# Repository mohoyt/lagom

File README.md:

# lagom
Lagom is an easy to build 65% keyboard using only through hole components. It uses a separate microcontroller (like the Pro Micro, Elite C or something RP2040 based) to enable flexibility in firmware and connectivity and to further simplify the soldering experience (no more tricksy USB ports). Demultiplexers and a custom matrix are used to enable the size and features of the board with only the pinouts of a pro micro. 

**Lagom kits are available for sale at [sthlmkb.com](https://sthlmkb.com/shop/lagom-keyboard-kit/)**

[License](LICENSE)

Lagom is licensed under the [Creative Commons Attribution-NonCommercial 4.0 International license](https://creativecommons.org/licenses/by-nc/4.0/). This design as it stands in this repository may be freely reproduced, modified, and manufactured for PERSONAL USE ONLY and may not be reproduced in physical form for public sale. 

## Features
* Only through hole components for easy soldering
* Separate microcontroller using Pro micro, Elite C, Nice! Nano or equivalent footprint. So micro USB, USB-C or Bluetooth are all options!
* 2 rotary encoders
* OLED screen
* Optional underglow RGB lighting with a WS2812b light strip
* Multiple layout options including ISO, ANSI, split space (2.25u + 1.25u + 2.75u), 7u space, split left shift (1.25u + 1u) and stepped capslock ([layout]("http://www.keyboard-layout-editor.com/##@_name=Lagom&notes=16%20cols%20%2F=%204%20pins%20with%202x%203%20to%208%20demux%20(2%5E4%20%2F=%2016)%0A5%20rows%0A11%20pins%20total%20for%20keyswitches%0A16%20+%202%20pins%20(for%20OLED)%20on%20a%20pro%20micro%0A1%20pin%20for%20LED%20underglow%0A4%20pins%20for%202%20encoders%0A%0A72%20keys%20+%202%20enc%20%3B&@_x:13.75%3B&=1,15&_x:0.25%3B&=2,15&_x:0.25%3B&=0,0%0A%0A%0A%0A%0A%0A%0A%0A%0Ae&=0,1%0A%0A%0A%0A%0A%0A%0A%0A%0Ae%3B&@_y:0.25%3B&=0,0&=0,1&=0,2&=0,3&=0,4&=0,5&=0,6&=0,7&=0,8&=0,9&=0,10&=0,11&=0,12&_w:2%3B&=0,14%0A%0A%0A0,0&=0,15&_x:0.25%3B&=1,0%0A%0A%0A%0A%0A%0A%0A%0A%0Ae&=1,1%0A%0A%0A%0A%0A%0A%0A%0A%0Ae%3B&@_w:1.5%3B&=1,0&=1,1&=1,2&=1,3&=1,4&=1,5&=1,6&=1,7&=1,8&=1,9&=1,10&=1,11&=1,12&_w:1.5%3B&=1,13%0A%0A%0A1,0&=1,14%3B&@_w:1.75%3B&=2,0&=2,1&=2,2&=2,3&=2,4&=2,5&=2,6&=2,7&=2,8&=2,9&=2,10&=2,11&_w:2.25%3B&=2,13%0A%0A%0A1,0&=2,14%3B&@_w:2.25%3B&=3,0%0A%0A%0A2,0&=3,2&=3,3&=3,4&=3,5&=3,6&=3,7&=3,8&=3,9&=3,10&=3,11&_w:1.75%3B&=3,12&=3,13&=3,14%3B&@_w:1.25%3B&=4,0%0A%0A%0A3,0&_w:1.25%3B&=4,1%0A%0A%0A3,0&_w:1.25%3B&=4,2%0A%0A%0A3,0&_w:6.25%3B&=4,6%0A%0A%0A3,0&_w:1.25%3B&=4,10%0A%0A%0A3,0&_w:1.25%3B&=4,11%0A%0A%0A3,0&_x:0.5%3B&=4,12&=4,13&=4,14%3B&@_y:0.5&w:1.25%3B&=4,0%0A%0A%0A3,1&_w:1.25%3B&=4,1%0A%0A%0A3,1&_w:1.25%3B&=4,2%0A%0A%0A3,1&_w:2.25%3B&=4,4%0A%0A%0A3,1&_w:1.25%3B&=4,6%0A%0A%0A3,1&_w:2.75%3B&=4,8%0A%0A%0A3,1&_w:1.25%3B&=4,10%0A%0A%0A3,1&_w:1.25%3B&=4,11%0A%0A%0A3,1%3B&@_y:-0.25&x:15&w:1.25&h:2&w2:1.5&h2:1&x2:-0.25%3B&=2,13%0A%0A%0A1,1%3B&@_y:-0.75&w:1.5%3B&=4,0%0A%0A%0A3,2&=4,1%0A%0A%0A3,2&_w:1.5%3B&=4,2%0A%0A%0A3,2&_w:7%3B&=4,6%0A%0A%0A3,2&_w:1.5%3B&=4,11%0A%0A%0A3,2%3B&@_y:-0.25&x:14%3B&=2,12%0A%0A%0A1,1%3B&@_w:1.25%3B&=3,0%0A%0A%0A2,1&=3,1%0A%0A%0A2,1&_x:9.75%3B&=0,13%0A%0A%0A0,1&=0,14%0A%0A%0A0,1"))
* Open and visible components (in the style of Plaid, Romac etc)
* Simple, beautiful and flexible sandwich case out of FR4 (pcb material)

## Components required 
* PCB
* FR4 Switch plate
* FR4 Base 
* Controller (I used a Pro Micro in the guide but anything that shares the footprint and pinout will be fine e.g. Elite C, Nice! Nano, or something RP2040 powered!)
* Diodes 1N4148 (74)
* 0.1μF Capacitor (2)
* 16 pin IC socket (2)
* IC (74HC138N) demultiplexer (2)
* Switches (5 pin MX footprint) (up to 72 depending on layout)
* Rotary encoders (2)
* Rotary encoder knobs (2)
* 0.91" OLED screen
* 10mm M2 Standoffs (9 required if mounting the base to the plate)
* 6mm x M2 screws for attaching the standoffs to the plate/base (2 per standoff so 18 total)
* Acrylic cover for the components at the top (optional, not included)
* Stabilisers (PCB mount) (5 x 2u or 3 x 2u + 6.25u or 3 x 2u + 7u depending on layout)
* Rubber feet for the base

[Build guide available here](build_guide.md)

## Dimensions
* PCB: 305.6mm x 121.78mm
* Plate: 319.925mm x 128.925mm (102.662mm height at the lower section)
* Base: 319.925mm x 128.925mm 

## Known issues 
None yet! 

## Where to buy
Lagom kits are available for sale exclusively at [sthlmkb.com](https://sthlmkb.com/shop/lagom-keyboard-kit/)

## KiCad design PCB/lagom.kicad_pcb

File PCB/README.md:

# lagom PCBs
Lagom is an easy to build 65% keyboard using only through hole components. It uses a separate microcontroller (like the Pro Micro, Elite C or something RP2040 based) to enable flexibility in firmware and connectivity and to further simplify the soldering experience (no more tricksy USB ports). Demultiplexers and a custom matrix are used to enable the size and features of the board with only the pinouts of a pro micro. 

**Lagom kits are available for sale at [sthlmkb.com](https://sthlmkb.com/shop/lagom-keyboard-kit/)**

[License](LICENSE)

Lagom is licensed under the [Creative Commons Attribution-NonCommercial 4.0 International license](https://creativecommons.org/licenses/by-nc/4.0/). This design as it stands in this repository may be freely reproduced, modified, and manufactured for PERSONAL USE ONLY and may not be reproduced in physical form for public sale. 

## Designs that are here:
* Lagom (i.e this directory) - this is the main PCB
* Lagom Plate (`lagom_plate`) - this is the plate that holds the switches and goes above the PCB
* Lagom Base (`lagom_base`) - this is the base of the board and goes below the PCB
* Lagom Window (`lagom_window`) - this is an optional design for an acrylic window that covers the diodes and the controller

## Some useful images/documentation:

This the key layout and all option layouts exported from keyboard-layout-editor

This the layout of the matrix used

This the pinout of the pro micro or pro micro compatible controller

This is the pinout of the demuxes used in Lagom to enable all the columns to work on a pro micro pinout

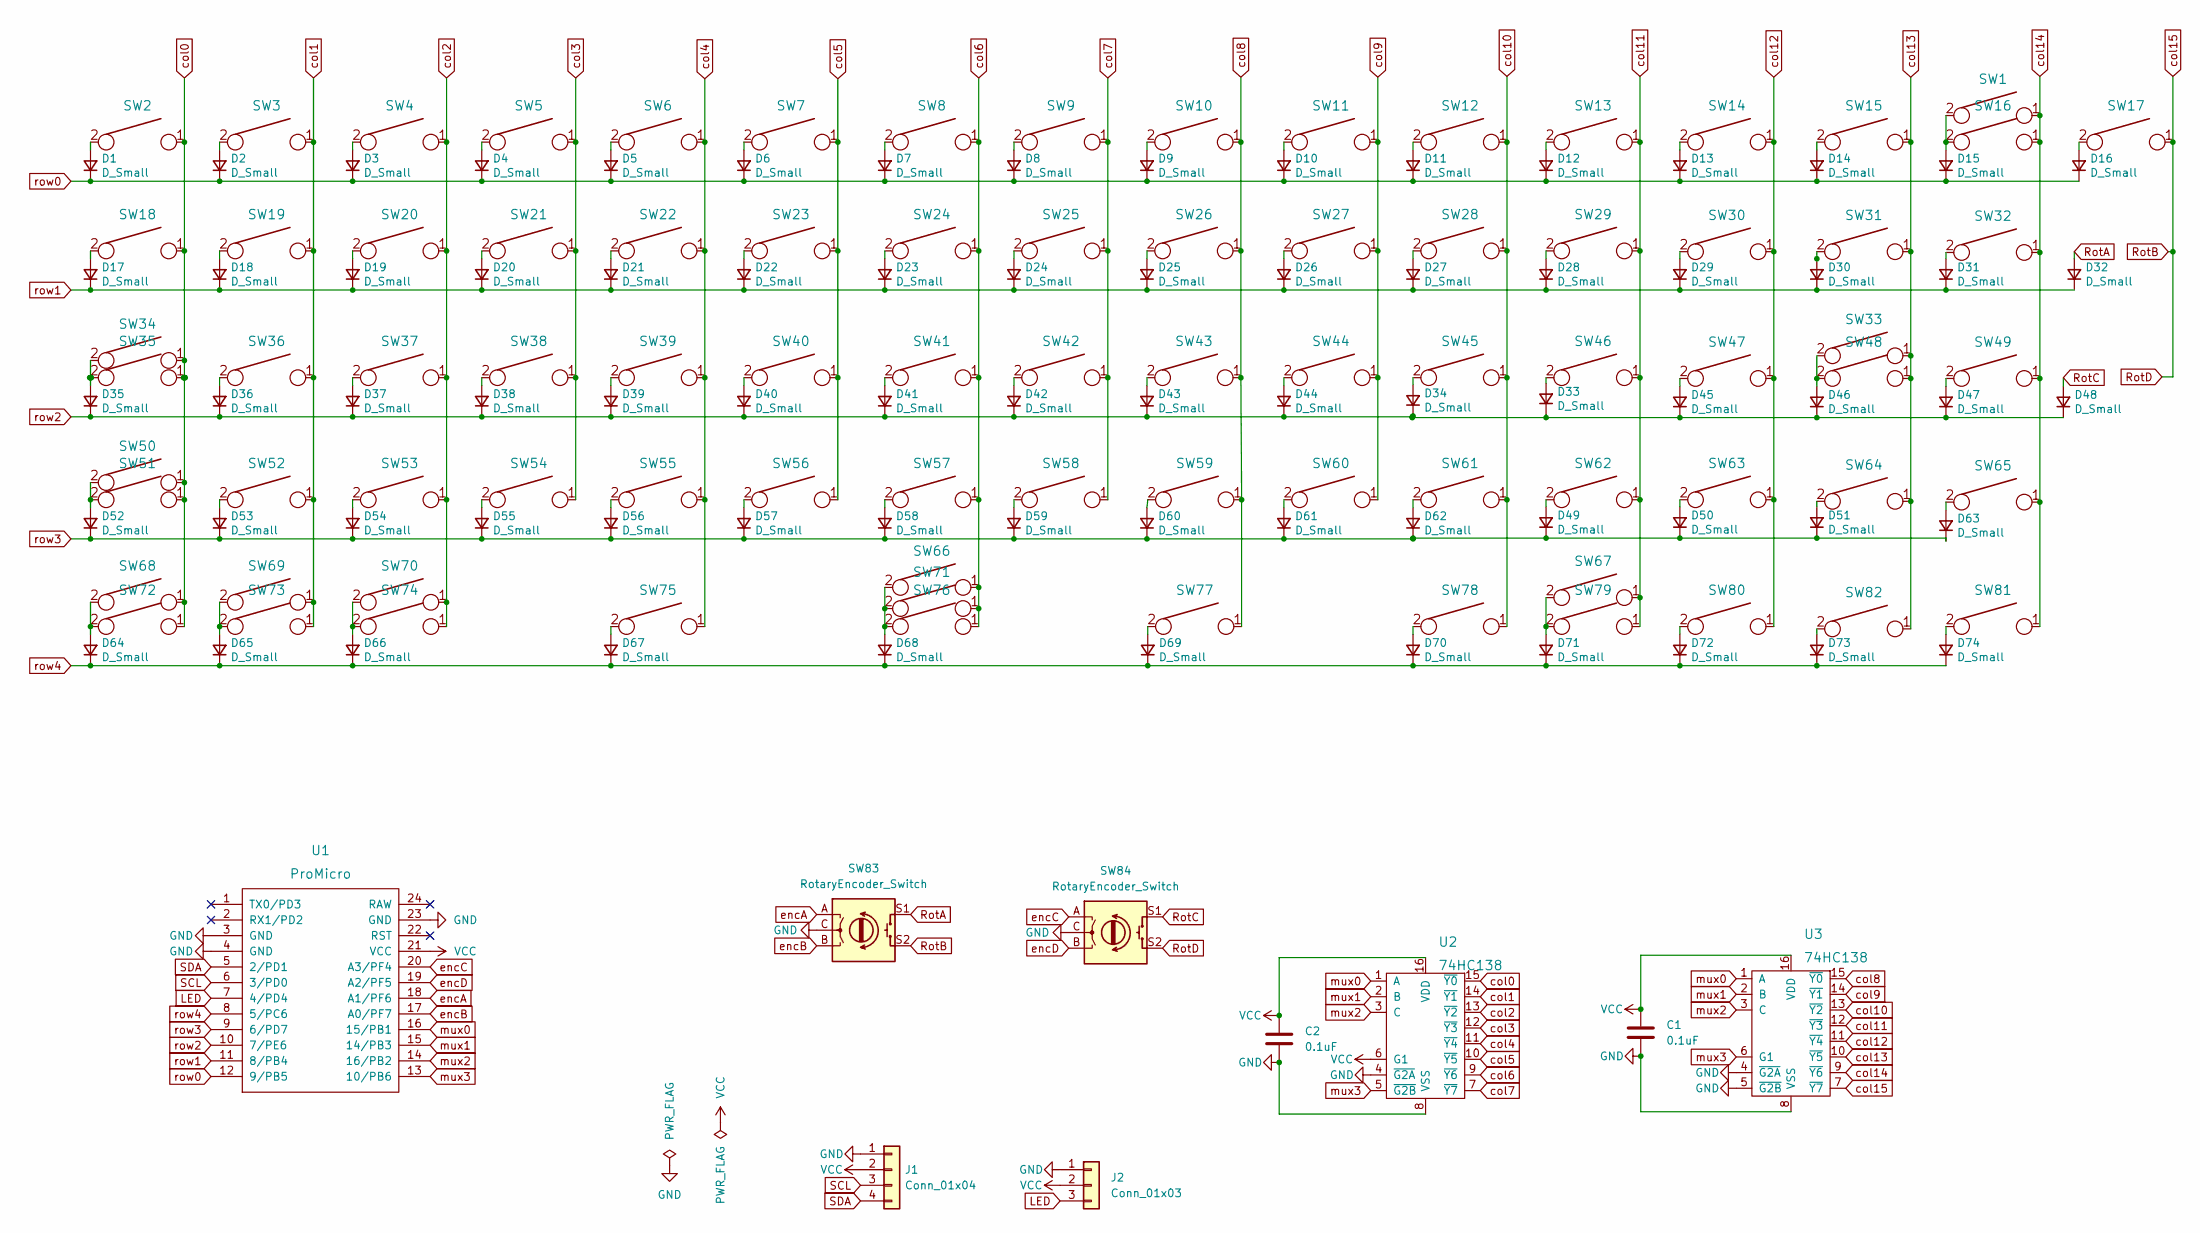
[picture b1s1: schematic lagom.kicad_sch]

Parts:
C1, C2: 0.1uF; C_Disc_D4.7mm_W2.5mm_P5.00mm
D1: D_Small; D_DO-35_SOD27_P7.62mm_Horizontal
D2, D3, D4, D5, D6, D7, D8, D9, D10, D11, D12, D13, D14, D15, D16, D17, D18, D19, D20, D21, D22, D23, D24, D25, D26, D27, D28, D29, D30, D31, D32, D33, D34, D35, D36, D37, D38, D39, D40, D41, D42, D43, D44, D45, D46, D47, D48, D49, D50, D51, D52, D53, D54, D55, D56, D57, D58, D59, D60, D61, D62, D63, D64, D65, D66, D67, D68, D69, D70, D71, D72, D73, D74: D_Small; D_DO-34_SOD68_P7.62mm_Horizontal
J1: Conn_01x04; PinSocket_1x04_P2.54mm_Vertical
J2: Conn_01x03; PinSocket_1x03_P2.54mm_Vertical
SW1: KEYSW; SW_Cherry_MX_2.00u_PCB
SW2, SW3, SW4, SW5, SW6, SW7, SW8, SW9, SW10, SW11, SW12, SW13, SW14, SW15, SW16, SW17, SW19, SW20, SW21, SW22, SW23, SW24, SW25, SW26, SW27, SW28, SW29, SW30, SW32, SW35, SW36, SW37, SW38, SW39, SW40, SW41, SW42, SW43, SW44, SW45, SW46, SW47, SW49, SW52, SW53, SW54, SW55, SW56, SW57, SW58, SW59, SW60, SW61, SW62, SW64, SW65, SW73, SW80, SW81, SW82: KEYSW; SW_Cherry_MX_1.00u_PCB
SW18: KEYSW; SW_Cherry_MX_1.50u_Plate
SW31, SW67, SW70, SW72: KEYSW; SW_Cherry_MX_1.50u_PCB
SW33: KEYSW; SW_Cherry_MX_ISOEnter_PCB
SW34, SW63: KEYSW; SW_Cherry_MX_1.75u_PCB
SW48, SW50, SW75: KEYSW; SW_Cherry_MX_2.25u_PCB
SW51, SW68, SW69, SW71, SW74, SW78, SW79: KEYSW; SW_Cherry_MX_1.25u_PCB
SW66: KEYSW; SW_Cherry_MX_7u_PCB
SW76: KEYSW; SW_Cherry_MX_6.25u_PCB
SW77: KEYSW; SW_Cherry_MX_2.75u_PCB
SW83, SW84: RotaryEncoder_Switch; RotaryEncoder_EC11
U1: ProMicro; ArduinoProMicro-ZigZag
U2, U3: 74HC138; DIP-16_W7.62mm_Socket

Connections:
GND: C1.2, C2.2, J1.1, J2.1, SW83.C, SW84.C, U1.3 (GND), U1.4 (GND), U1.23 (GND), U2.4 (~G2A), U2.8 (VSS), U3.4 (~G2A), U3.5 (~G2B), U3.8 (VSS)
LED: J2.3, U1.7 (4/PD4)
unnamed: D1.2 (A), SW2.2
unnamed: D2.2 (A), SW3.2
unnamed: D3.2 (A), SW4.2
unnamed: D4.2 (A), SW5.2
unnamed: D5.2 (A), SW6.2
unnamed: D6.2 (A), SW7.2
unnamed: D7.2 (A), SW8.2
unnamed: D8.2 (A), SW9.2
unnamed: D9.2 (A), SW10.2
unnamed: D10.2 (A), SW11.2
unnamed: D11.2 (A), SW12.2
unnamed: D12.2 (A), SW13.2
unnamed: D13.2 (A), SW14.2
unnamed: D14.2 (A), SW15.2
unnamed: D15.2 (A), SW1.2, SW16.2
unnamed: D16.2 (A), SW17.2
unnamed: D17.2 (A), SW18.2
unnamed: D18.2 (A), SW19.2
unnamed: D19.2 (A), SW20.2
unnamed: D20.2 (A), SW21.2
unnamed: D21.2 (A), SW22.2
unnamed: D22.2 (A), SW23.2
unnamed: D23.2 (A), SW24.2
unnamed: D24.2 (A), SW25.2
unnamed: D25.2 (A), SW26.2
unnamed: D26.2 (A), SW27.2
unnamed: D27.2 (A), SW28.2
unnamed: D28.2 (A), SW29.2
unnamed: D29.2 (A), SW30.2
unnamed: D30.2 (A), SW31.2
unnamed: D31.2 (A), SW32.2
unnamed: D33.2 (A), SW46.2
unnamed: D34.2 (A), SW45.2
unnamed: D35.2 (A), SW34.2, SW35.2
unnamed: D36.2 (A), SW36.2
unnamed: D37.2 (A), SW37.2
unnamed: D38.2 (A), SW38.2
unnamed: D39.2 (A), SW39.2
unnamed: D40.2 (A), SW40.2
unnamed: D41.2 (A), SW41.2
unnamed: D42.2 (A), SW42.2
unnamed: D43.2 (A), SW43.2
unnamed: D44.2 (A), SW44.2
unnamed: D45.2 (A), SW47.2
unnamed: D46.2 (A), SW33.2, SW48.2
unnamed: D47.2 (A), SW49.2
unnamed: D49.2 (A), SW62.2
unnamed: D50.2 (A), SW63.2
unnamed: D51.2 (A), SW64.2
unnamed: D52.2 (A), SW50.2, SW51.2
unnamed: D53.2 (A), SW52.2
unnamed: D54.2 (A), SW53.2
unnamed: D55.2 (A), SW54.2
unnamed: D56.2 (A), SW55.2
unnamed: D57.2 (A), SW56.2
unnamed: D58.2 (A), SW57.2
unnamed: D59.2 (A), SW58.2
unnamed: D60.2 (A), SW59.2
unnamed: D61.2 (A), SW60.2
unnamed: D62.2 (A), SW61.2
unnamed: D63.2 (A), SW65.2
unnamed: D64.2 (A), SW68.2, SW72.2
unnamed: D65.2 (A), SW69.2, SW73.2
unnamed: D66.2 (A), SW70.2, SW74.2
unnamed: D67.2 (A), SW75.2
unnamed: D68.2 (A), SW66.2, SW71.2, SW76.2
unnamed: D69.2 (A), SW77.2
unnamed: D70.2 (A), SW78.2
unnamed: D71.2 (A), SW67.2, SW79.2
unnamed: D72.2 (A), SW80.2
unnamed: D73.2 (A), SW82.2
unnamed: D74.2 (A), SW81.2
RotA: D32.2 (A), SW83.S1
RotB: SW17.1, SW83.S2, SW84.S2, U3.7 (~Y7)
RotC: D48.2 (A), SW84.S1
SCL: J1.3, U1.6 (3/PD0)
SDA: J1.4, U1.5 (2/PD1)
VCC: C1.1, C2.1, J1.2, J2.2, U1.21 (VCC), U2.6 (G1), U2.16 (VDD), U3.16 (VDD)
col0: SW2.1, SW18.1, SW34.1, SW35.1, SW50.1, SW51.1, SW68.1, SW72.1, U2.15 (~Y0)
col1: SW3.1, SW19.1, SW36.1, SW52.1, SW69.1, SW73.1, U2.14 (~Y1)
col2: SW4.1, SW20.1, SW37.1, SW53.1, SW70.1, SW74.1, U2.13 (~Y2)
col3: SW5.1, SW21.1, SW38.1, SW54.1, U2.12 (~Y3)
col4: SW6.1, SW22.1, SW39.1, SW55.1, SW75.1, U2.11 (~Y4)
col5: SW7.1, SW23.1, SW40.1, SW56.1, U2.10 (~Y5)
col6: SW8.1, SW24.1, SW41.1, SW57.1, SW66.1, SW71.1, SW76.1, U2.9 (~Y6)
col7: SW9.1, SW25.1, SW42.1, SW58.1, U2.7 (~Y7)
col8: SW10.1, SW26.1, SW43.1, SW59.1, SW77.1, U3.15 (~Y0)
col9: SW11.1, SW27.1, SW44.1, SW60.1, U3.14 (~Y1)
col10: SW12.1, SW28.1, SW45.1, SW61.1, SW78.1, U3.13 (~Y2)
col11: SW13.1, SW29.1, SW46.1, SW62.1, SW67.1, SW79.1, U3.12 (~Y3)
col12: SW14.1, SW30.1, SW47.1, SW63.1, SW80.1, U3.11 (~Y4)
col13: SW15.1, SW31.1, SW33.1, SW48.1, SW64.1, SW82.1, U3.10 (~Y5)
col14: SW1.1, SW16.1, SW32.1, SW49.1, SW65.1, SW81.1, U3.9 (~Y6)
encA: SW83.A, U1.18 (A1/PF6)
encB: SW83.B, U1.17 (A0/PF7)
encC: SW84.A, U1.20 (A3/PF4)
encD: SW84.B, U1.19 (A2/PF5)
mux0: U1.16 (15/PB1), U2.1 (A), U3.1 (A)
mux1: U1.15 (14/PB3), U2.2 (B), U3.2 (B)
mux2: U1.14 (16/PB2), U2.3 (C), U3.3 (C)
mux3: U1.13 (10/PB6), U2.5 (~G2B), U3.6 (G1)
row0: D1.1 (K), D2.1 (K), D3.1 (K), D4.1 (K), D5.1 (K), D6.1 (K), D7.1 (K), D8.1 (K), D9.1 (K), D10.1 (K), D11.1 (K), D12.1 (K), D13.1 (K), D14.1 (K), D15.1 (K), D16.1 (K), U1.12 (9/PB5)
row1: D17.1 (K), D18.1 (K), D19.1 (K), D20.1 (K), D21.1 (K), D22.1 (K), D23.1 (K), D24.1 (K), D25.1 (K), D26.1 (K), D27.1 (K), D28.1 (K), D29.1 (K), D30.1 (K), D31.1 (K), D32.1 (K), U1.11 (8/PB4)
row2: D33.1 (K), D34.1 (K), D35.1 (K), D36.1 (K), D37.1 (K), D38.1 (K), D39.1 (K), D40.1 (K), D41.1 (K), D42.1 (K), D43.1 (K), D44.1 (K), D45.1 (K), D46.1 (K), D47.1 (K), D48.1 (K), U1.10 (7/PE6)
row3: D49.1 (K), D50.1 (K), D51.1 (K), D52.1 (K), D53.1 (K), D54.1 (K), D55.1 (K), D56.1 (K), D57.1 (K), D58.1 (K), D59.1 (K), D60.1 (K), D61.1 (K), D62.1 (K), D63.1 (K), U1.9 (6/PD7)
row4: D64.1 (K), D65.1 (K), D66.1 (K), D67.1 (K), D68.1 (K), D69.1 (K), D70.1 (K), D71.1 (K), D72.1 (K), D73.1 (K), D74.1 (K), U1.8 (5/PC6)

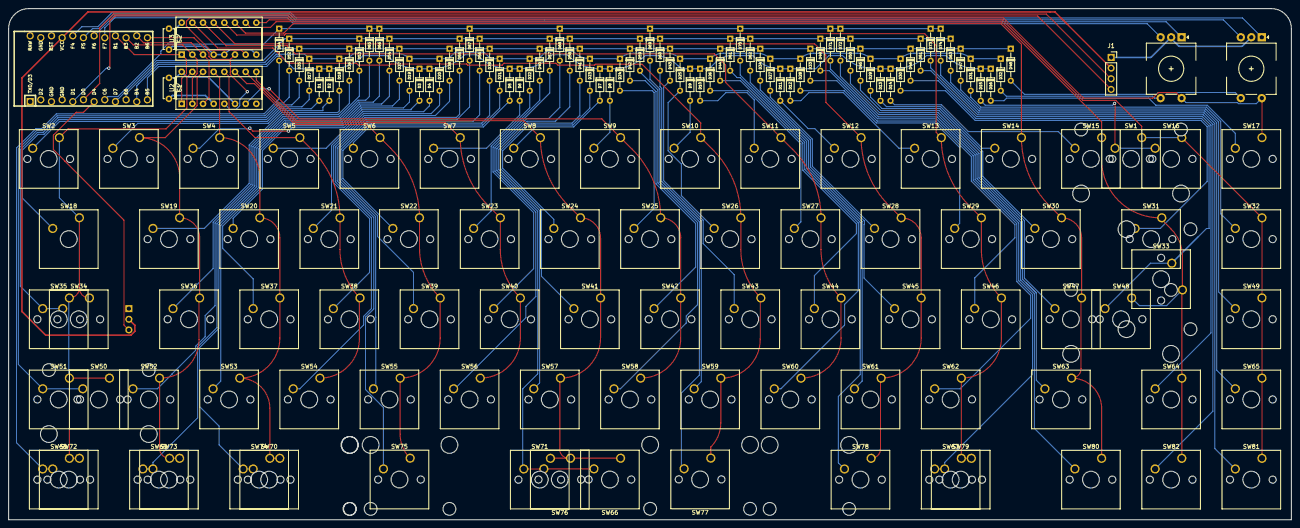
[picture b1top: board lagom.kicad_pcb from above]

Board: 2 copper layers, 305.6 x 121.8 mm, 165 parts (1 on the bottom side), 108 nets.

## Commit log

2022-08-01 Submodules
2022-08-01 Init Kicad
2022-08-01 Grid started
2022-08-06 Matrix almost done
2022-08-07 Matrix complete, wiring schematic
2022-08-07 Schematic complete
2022-08-22 PCB layout done
2022-08-28 Firmware v1 done
2022-08-29 demux pin change
2022-09-03 Layout and diode placement basically done
2022-09-04 PCB mostly done
2022-10-10 Graphics and plate
2022-10-15 base, plate and more added
2022-10-16 Labelling mostly done
2022-10-17 V1 done
2022-10-18 Missing holes for tab key
2022-10-18 v1 gerbers updated
2022-10-18 readme updated
2022-11-01 Firmware built
2022-11-10 Working firmware and updated build guide
2022-11-11 updated (and simplified) firmware
2022-11-11 Firmware fixing
2022-11-13 Build guide pictures added
2022-11-13 Build guide updated, license added
2022-11-13 vial wpmhud firmware added
2022-11-20 Build guide updated to show LED socket
2022-12-28 Lagom window updated
2023-01-10 Updated rotary encoder direction in vial firmware files
2023-05-16 Pinout and matrix images added
2023-08-10 Flashing guide added
2023-08-10 BVroken guide image fixed
2023-08-21 New bongocat vial firmware added
2023-08-26 Closeup diode photo added
2023-10-13 PCB readme updated
2023-11-04 Update matrix.c
    Make compatible with ARM / rp2040 based boards.
2023-11-10 Readme updated to add info about vial-qmk and a vial bongocat added to the keymaps folder
2023-11-11 RGB lighting info added to firmware README
2023-11-11 RGB lighting info added to firmware README again
2024-03-25 RP2040 compatible precompiled firmware added
2024-04-03 Updated flashing insructions
2024-04-11 Debug firmware added
2025-04-09 Test firmware versions added to support USB timeout issues
2025-07-25 Dimensions added to Readme
